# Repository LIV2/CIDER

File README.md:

# CDTV IDE + RAM
IDE + 11.37 Megabyte Fast RAM + Dual Kickstart flash for the CDTV

## Features

- Plugs in to the Diagnostic port
- Autoboot IDE, Kick 1.3 compatible Open Source driver [lide.device](https://github.com/LIV2/lide.device)
- 11.37MB Fast RAM - 1.5MB $C0/Ranger + 8MB Fast + 1.87 Bonus ($A00000)
- Dual Kickstart Flash ROM with Extended ROM, programmable in-system

## Table of contents
1. [Compatibility](#compatibility)
2. [Quick start](#quick-start)
3. [Switch settings](#switch-settings)
    * [DIP Switches](#dip-switches)
    * [JP15](#jp15)
4. [Programming](#programming)
5. [Software](#software)
6. [Common issues](#common-issues)
7. [Ordering pcbs](#ordering-pcbs)
    * [PCB Order details](#pcb-order-details)
    * [PCB Assembly](#pcb-assembly)
    * [Bill of materials](#bill-of-materials)
8. [Pictures](#pictures)
9. [Acknowledgements](#acknowledgements)
10. [License](#license)

## Compatibility

Compatible with kickstart 1.3 and up.

## Quick start
* Remove the power cord from your CDTV
* Ensure the kick flash switch is turned off before using for the first time, all other dip-switches may be enabled if you wish
* Plug into the diag port in your CDTV
* Connect jumper-wire from CDTV JP15 and "To JP15" header, or remove the jumper from the CDTV's JP15 header
* Boot from the CIDER-IDE-Update.adf [here](https://github.com/LIV2/CIDER-Software/releases) to install the IDE ROM
* Download the software tools from the [CIDER-Software](https://github.com/LIV2/cider-software/releases) release page
* Consult the software [documentation](https://github.com/LIV2/CIDER-Software/blob/main/README.md)

## Switch settings
* A500 Mode: Disables the CDTV extended rom
* ROM Select: Selects the second bank of the Kickstart Flash when closed

### DIP Switches
1. Fast RAM enable
2. Ranger / $C0 RAM enable
3. IDE enable
4. Kick flash enable

### JP15
CIDER needs to disable the CDTV's own extended roms when in A500 mode, or when CIDER's Kick flash is enabled so that it can take over this function  
If you don't have a cable to connect this, you can simply remove the JP15 jumper (but the ext rom will then be disabled even if kick flash is switched off)

## Programming

Program the CPLD using this [jed file](https://github.com/LIV2/CIDER/raw/main/Binary/CIDER.jed) - You can find instructions on how to do that [here](https://linuxjedi.co.uk/2020/12/01/programming-xilinx-jtag-from-a-raspberry-pi/)

IDE ROM can be programmed by booting from the latest CIDER-IDE-Update.adf [here](https://github.com/LIV2/CIDER-Software/releases).

## Software

Various software tools for CIDER are available in the [CIDER-Software](https://github.com/LIV2/CIDER-Software) repository, you can find disk images and .lha files under the Releases section.

## Common issues

* **CDTV doesn't boot from IDE:** The original CDTV bootstrap does not boot from hard disks by default, only the builtin scsi.device, floppy or cdrom.  
To boot from the HDD I recommend making use of the 2.35 Extended rom from [CDTV Land](https://cdtvland.com/os235/)

## Ordering PCBs

Download the latest Gerbers.zip from the latest release listed on the right-hand side of this page.

Also included in the release are the placement and bom files needed for JLCPCB's assembly service

### PCB Order details
This PCB has been designed to JLCPCB's 4-layer capabilities so I recommend ordering from them

* Layers: 4
* Surface finish: ENIG
* Remove Order Number: Specify a location

### PCB Assembly
The release files include the relevant BOM and CPL files for JLCPCB's Assembly service  
You can use the following options:  
* PCBA Type: Economic
* Assembly side: Top side
* Tooling Holes: Added by Customer
* Confirm Parts Placement: Yes (I recommend checking that all ICs have pin 1 in the correct location etc)

### Bill of materials
|References|Qty|Value|Footprint|Link|Notes|
|----------|---|-----|---------|----|-----|
|CN1|1|CDTV Connector|KEL 8801-080-170S-F| |Contact KEL to order|
|C1,C3,C4,C6,C7,C8,C10,C11-14,C16-26,C28|23|0.1uF Ceramic|0603|[Mouser](https://www.mouser.com/ProductDetail/80-C603C104K5RAC3121)| |
|C2,C5,C27|3|47uF Tantalum|EIA-3216 KEMET A|[Mouser](https://www.mouser.com/ProductDetail/80-T490A476M10ATE1K)| |
|C9,C15|3|10uF Tantalum|EIA-3216 KEMET A|[Mouser](https://www.mouser.com/ProductDetail/581-TAJA106K016R)| |
|R2,R3,R5-12|10|10K|0603|[Mouser](https://www.mouser.com/ProductDetail/279-CRGH0603J10K)| |
|R13,R14|2|1K|0603|[Mouser](https://www.mouser.com/ProductDetail/791-WR06X102JTL)| |
|R1|1|33|0603|[Mouser](https://www.mouser.com/ProductDetail/279-CRG0603F33R)| |
|R4|1|220|0603|[Mouser](https://www.mouser.com/ProductDetail/71-CRCW0603-220-E3)| |
|D1|1|SMD LED|0603|[Mouser](https://www.mouser.com/ProductDetail/710-150060VS75003)| |
|U3-5|3|74HCT245|TSSOP-20|[Mouser](https://www.mouser.com/ProductDetail/595-SN74HCT245PWR)| |
|U6-7|3|74LVC245|TSSOP-20|[Mouser](https://www.mouser.com/ProductDetail/595-SN74LVC245APWR)| |
|U1|1|AZ1117CR-3.3|SOT-89-3|[Mouser](https://www.mouser.com/ProductDetail/621-AZ1117CR-3.3TRG1)| |
|U2|1|XC95144XL-10TQ100|TQFP-100|[Mouser](https://www.mouser.com/ProductDetail/217-5144XL-10TQG100C)|
|U8|1|8Mx16 SDRAM A3V28S40JTP-60|TSOP-II-54|[Mouser](https://www.mouser.com/ProductDetail/155-A3V28S40JTP-60)|Also suitable:</br> MT48LC8M16</br>W9812G6KH|
|U9|1|29F160|TSOP-I-48|[Mouser](https://www.mouser.com/ProductDetail/913-M29F160FB5AN6F2)| |
|U10|1|39SF010|TSOP-I-32|[Mouser](https://www.mouser.com/ProductDetail/804-39SF010A7CWHE)| |
|U11|1|74LVC1G32|SOT-23-5|[Mouser](https://www.mouser.com/ProductDetail/595-SN74LVC1G32DBVR)| |
|X1|1|50MHz Oscillator|3.2x2.5mm|[Mouser](https://www.mouser.com/ProductDetail/520-ECS-2333-500-BNT)| |
|F1|1|Polyfuse 1A trip, 500mA hold|1206|[Mouser](https://www.mouser.com/ProductDetail/576-1206L075/13.2WR)| |
|SW1|1|Omron A6H-4101|A6H-4101|[Mouser](https://www.mouser.com/ProductDetail/653-A6H-4101)| |
|RN1|1|10K|R Array Convex 4x0603|[Mouser](https://www.mouser.com/ProductDetail/667-EXB-V8V103GV)| |
|RN2-5|4|22 Ohm|R Array Convex 4x0603|[Mouser](https://www.mouser.com/ProductDetail/667-EXB-V8N220JV)| |
|J2-J3|2|Header|2.0mm 1x02 Right-angle| | |
|J5|1|Header|2.54mm 1x03 Right-angle| | |

## Pictures

## Acknowledgements

Thanks to [Stefan Reinauer](https://github.com/reinauer) for the idea to make a CDTV expansion, helping me to develop & test this and for sourcing some Connectors!  
The addition of the Kickstart Flash was inspired by [jbilander](https://github.com/jbilander)'s awesome [Spitfire 2000](https://github.com/jbilander/SF2000)  
Thank you to [Eriond](https://github.com/eriond) for providing the 3D Model of the KEL connector! 

## License

CIDER is licensed under the GPL-2.0 only license

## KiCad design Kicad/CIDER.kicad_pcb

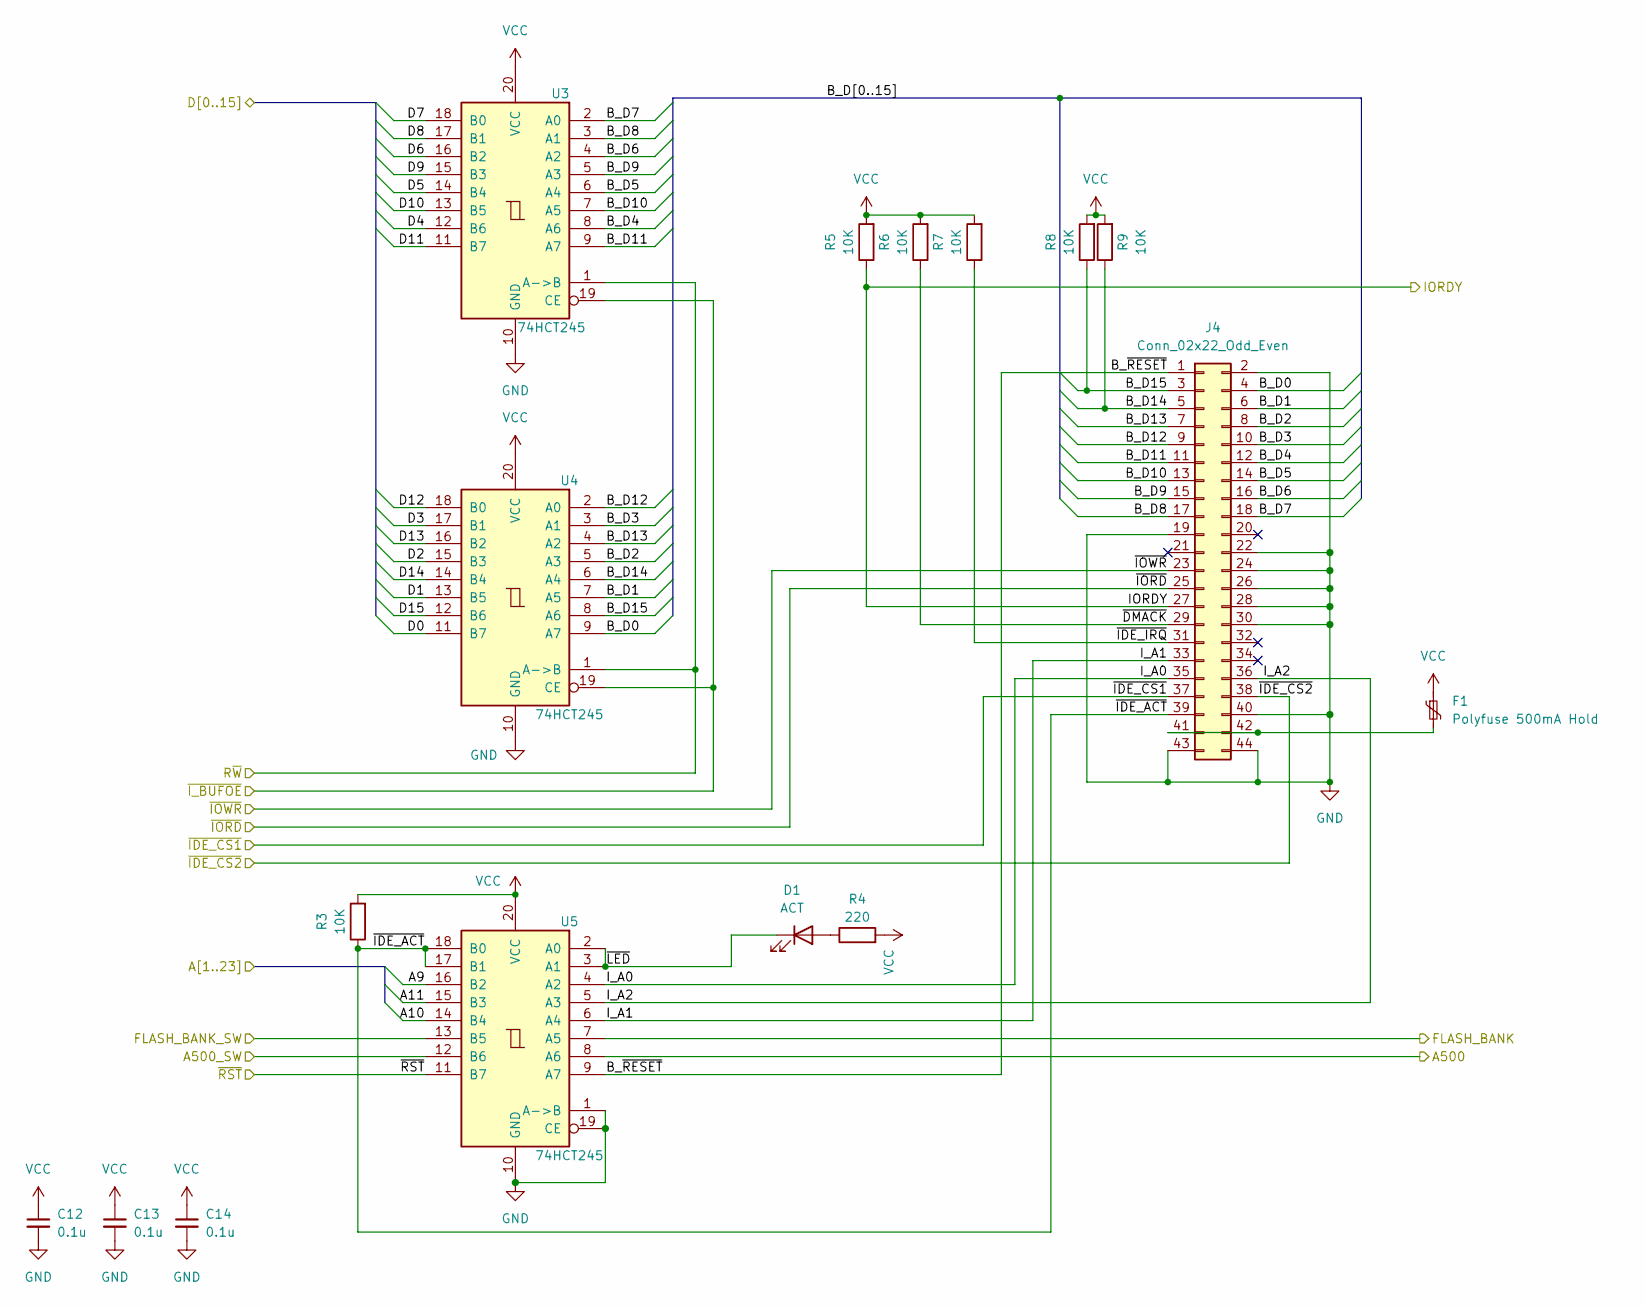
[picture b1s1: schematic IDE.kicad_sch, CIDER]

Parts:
C12, C13, C14: 0.1u; C_0603_1608Metric; LCSC # C14663
D1: ACT; LED_0603_1608Metric; LCSC # C264450
F1: Polyfuse 500mA Hold; Fuse_1206_3216Metric; LCSC # C151162
J4: Conn_02x22_Odd_Even; PinHeader_2x22_P2.00mm_Vertical
R3, R5, R6, R7, R8, R9: 10K; R_0603_1608Metric; LCSC # C25804
R4: 220; R_0603_1608Metric; LCSC # C22962
U3, U4, U5: 74HCT245; TSSOP-20_4.4x6.5mm_P0.65mm; LCSC # C6779

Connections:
/Amiga+CPLD/A9: U5.16 (B2); also elsewhere on the board
/Amiga+CPLD/A10: U5.14 (B4); also elsewhere on the board
/Amiga+CPLD/A11: U5.15 (B3); also elsewhere on the board
/Amiga+CPLD/A500: U5.8 (A6); also elsewhere on the board
/Amiga+CPLD/A500_SW: U5.12 (B6); also elsewhere on the board
/Amiga+CPLD/D0: U4.11 (B7); also elsewhere on the board
/Amiga+CPLD/D1: U4.13 (B5); also elsewhere on the board
/Amiga+CPLD/D2: U4.15 (B3); also elsewhere on the board
/Amiga+CPLD/D3: U4.17 (B1); also elsewhere on the board
/Amiga+CPLD/D4: U3.12 (B6); also elsewhere on the board
/Amiga+CPLD/D5: U3.14 (B4); also elsewhere on the board
/Amiga+CPLD/D6: U3.16 (B2); also elsewhere on the board
/Amiga+CPLD/D7: U3.18 (B0); also elsewhere on the board
/Amiga+CPLD/D8: U3.17 (B1); also elsewhere on the board
/Amiga+CPLD/D9: U3.15 (B3); also elsewhere on the board
/Amiga+CPLD/D10: U3.13 (B5); also elsewhere on the board
/Amiga+CPLD/D11: U3.11 (B7); also elsewhere on the board
/Amiga+CPLD/D12: U4.18 (B0); also elsewhere on the board
/Amiga+CPLD/D13: U4.16 (B2); also elsewhere on the board
/Amiga+CPLD/D14: U4.14 (B4); also elsewhere on the board
/Amiga+CPLD/D15: U4.12 (B6); also elsewhere on the board
/Amiga+CPLD/FLASH_BANK: U5.7 (A5); also elsewhere on the board
/Amiga+CPLD/FLASH_BANK_SW: U5.13 (B5); also elsewhere on the board
/Amiga+CPLD/IORDY: J4.27, R5.1; also elsewhere on the board
/Amiga+CPLD/R~W: U3.1 (A->B), U4.1 (A->B); also elsewhere on the board
/Amiga+CPLD/~IDE_CS1: J4.37; also elsewhere on the board
/Amiga+CPLD/~IDE_CS2: J4.38; also elsewhere on the board
/Amiga+CPLD/~IORD: J4.25; also elsewhere on the board
/Amiga+CPLD/~IOWR: J4.23; also elsewhere on the board
/Amiga+CPLD/~I_BUFOE: U3.19 (CE), U4.19 (CE); also elsewhere on the board
/Amiga+CPLD/~RST: U5.11 (B7); also elsewhere on the board
/IDE/B_D0: J4.4, U4.9 (A7)
/IDE/B_D1: J4.6, U4.7 (A5)
/IDE/B_D2: J4.8, U4.5 (A3)
/IDE/B_D3: J4.10, U4.3 (A1)
/IDE/B_D4: J4.12, U3.8 (A6)
/IDE/B_D5: J4.14, U3.6 (A4)
/IDE/B_D6: J4.16, U3.4 (A2)
/IDE/B_D7: J4.18, U3.2 (A0)
/IDE/B_D8: J4.17, U3.3 (A1)
/IDE/B_D9: J4.15, U3.5 (A3)
/IDE/B_D10: J4.13, U3.7 (A5)
/IDE/B_D11: J4.11, U3.9 (A7)
/IDE/B_D12: J4.9, U4.2 (A0)
/IDE/B_D13: J4.7, U4.4 (A2)
/IDE/B_D14: J4.5, R9.1, U4.6 (A4)
/IDE/B_D15: J4.3, R8.1, U4.8 (A6)
/IDE/B_~RESET: J4.1, U5.9 (A7)
/IDE/I_A0: J4.35, U5.4 (A2)
/IDE/I_A1: J4.33, U5.6 (A4)
/IDE/I_A2: J4.36, U5.5 (A3)
/IDE/~DMACK: J4.29, R6.1
/IDE/~IDE_ACT: J4.39, R3.1, U5.17 (B1), U5.18 (B0)
/IDE/~IDE_IRQ: J4.31, R7.1
/IDE/~LED: D1.1 (K), U5.2 (A0), U5.3 (A1)
GND: C12.2, C13.2, C14.2, J4.2, J4.19, J4.22, J4.24, J4.26, J4.28, J4.30, J4.40, J4.43, J4.44, U3.10 (GND), U4.10 (GND), U5.1 (A->B), U5.10 (GND), U5.19 (CE); also elsewhere on the board
unnamed: D1.2 (A), R4.1
unnamed: F1.2, J4.41, J4.42
VCC: C12.1, C13.1, C14.1, F1.1, R3.2, R4.2, R5.2, R6.2, R7.2, R8.2, R9.2, U3.20 (VCC), U4.20 (VCC), U5.20 (VCC); also elsewhere on the board

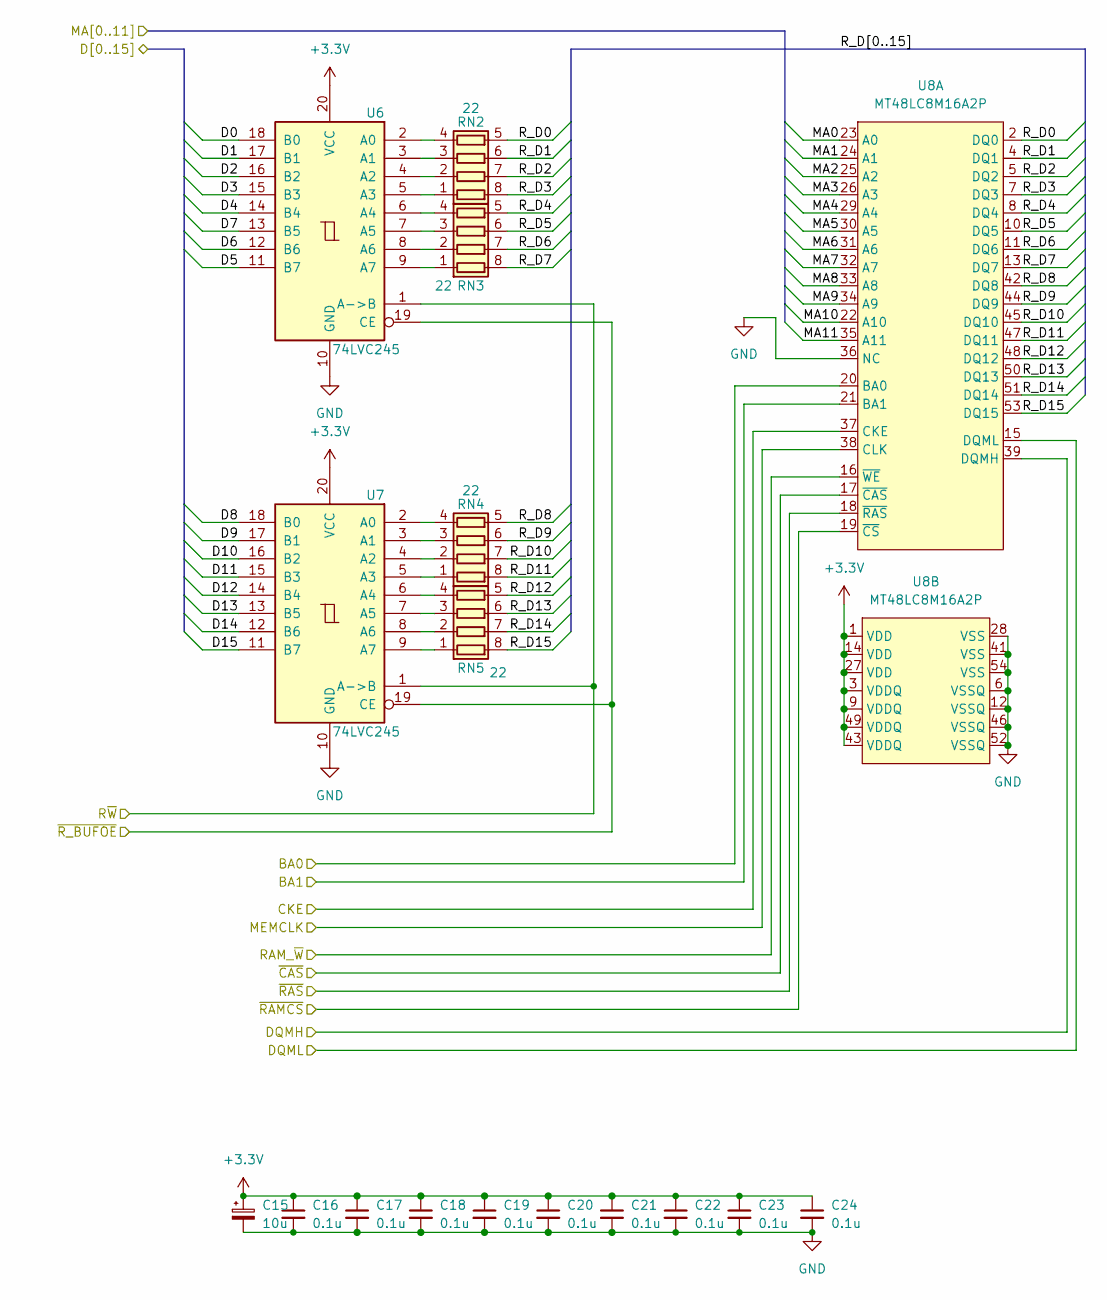
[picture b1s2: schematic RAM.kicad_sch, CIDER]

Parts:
C15: 10u; CP_EIA-3216-18_Kemet-A; LCSC # C7171
C16, C17, C18, C19, C20, C21, C22, C23, C24: 0.1u; C_0603_1608Metric; LCSC # C14663
RN2, RN3, RN4, RN5: 22; R_Array_Convex_4x0603; LCSC # C107373
U6, U7: 74LVC245; TSSOP-20_4.4x6.5mm_P0.65mm; LCSC # C7848
U8: MT48LC8M16A2P; TSOP-II-54_22.2x10.16mm_P0.8mm; LCSC # C62379

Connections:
/Amiga+CPLD/BA0: U8.20 (BA0); also elsewhere on the board
/Amiga+CPLD/BA1: U8.21 (BA1); also elsewhere on the board
/Amiga+CPLD/CKE: U8.37 (CKE); also elsewhere on the board
/Amiga+CPLD/D0: U6.18 (B0); also elsewhere on the board
/Amiga+CPLD/D1: U6.17 (B1); also elsewhere on the board
/Amiga+CPLD/D2: U6.16 (B2); also elsewhere on the board
/Amiga+CPLD/D3: U6.15 (B3); also elsewhere on the board
/Amiga+CPLD/D4: U6.14 (B4); also elsewhere on the board
/Amiga+CPLD/D5: U6.11 (B7); also elsewhere on the board
/Amiga+CPLD/D6: U6.12 (B6); also elsewhere on the board
/Amiga+CPLD/D7: U6.13 (B5); also elsewhere on the board
/Amiga+CPLD/D8: U7.18 (B0); also elsewhere on the board
/Amiga+CPLD/D9: U7.17 (B1); also elsewhere on the board
/Amiga+CPLD/D10: U7.16 (B2); also elsewhere on the board
/Amiga+CPLD/D11: U7.15 (B3); also elsewhere on the board
/Amiga+CPLD/D12: U7.14 (B4); also elsewhere on the board
/Amiga+CPLD/D13: U7.13 (B5); also elsewhere on the board
/Amiga+CPLD/D14: U7.12 (B6); also elsewhere on the board
/Amiga+CPLD/D15: U7.11 (B7); also elsewhere on the board
/Amiga+CPLD/DQMH: U8.39 (DQMH); also elsewhere on the board
/Amiga+CPLD/DQML: U8.15 (DQML); also elsewhere on the board
/Amiga+CPLD/MA0: U8.23 (A0); also elsewhere on the board
/Amiga+CPLD/MA1: U8.24 (A1); also elsewhere on the board
/Amiga+CPLD/MA2: U8.25 (A2); also elsewhere on the board
/Amiga+CPLD/MA3: U8.26 (A3); also elsewhere on the board
/Amiga+CPLD/MA4: U8.29 (A4); also elsewhere on the board
/Amiga+CPLD/MA5: U8.30 (A5); also elsewhere on the board
/Amiga+CPLD/MA6: U8.31 (A6); also elsewhere on the board
/Amiga+CPLD/MA7: U8.32 (A7); also elsewhere on the board
/Amiga+CPLD/MA8: U8.33 (A8); also elsewhere on the board
/Amiga+CPLD/MA9: U8.34 (A9); also elsewhere on the board
/Amiga+CPLD/MA10: U8.22 (A10); also elsewhere on the board
/Amiga+CPLD/MA11: U8.35 (A11); also elsewhere on the board
/Amiga+CPLD/MEMCLK: U8.38 (CLK); also elsewhere on the board
/Amiga+CPLD/RAM_~W: U8.16 (~WE); also elsewhere on the board
/Amiga+CPLD/R~W: U6.1 (A->B), U7.1 (A->B); also elsewhere on the board
/Amiga+CPLD/~CAS: U8.17 (~CAS); also elsewhere on the board
/Amiga+CPLD/~RAMCS: U8.19 (~CS); also elsewhere on the board
/Amiga+CPLD/~RAS: U8.18 (~RAS); also elsewhere on the board
/Amiga+CPLD/~R_BUFOE: U6.19 (CE), U7.19 (CE); also elsewhere on the board
/RAM/R_D0: RN2.5 (R4.2), U8.2 (DQ0)
/RAM/R_D1: RN2.6 (R3.2), U8.4 (DQ1)
/RAM/R_D2: RN2.7 (R2.2), U8.5 (DQ2)
/RAM/R_D3: RN2.8 (R1.2), U8.7 (DQ3)
/RAM/R_D4: RN3.5 (R4.2), U8.8 (DQ4)
/RAM/R_D5: RN3.6 (R3.2), U8.10 (DQ5)
/RAM/R_D6: RN3.7 (R2.2), U8.11 (DQ6)
/RAM/R_D7: RN3.8 (R1.2), U8.13 (DQ7)
/RAM/R_D8: RN4.5 (R4.2), U8.42 (DQ8)
/RAM/R_D9: RN4.6 (R3.2), U8.44 (DQ9)
/RAM/R_D10: RN4.7 (R2.2), U8.45 (DQ10)
/RAM/R_D11: RN4.8 (R1.2), U8.47 (DQ11)
/RAM/R_D12: RN5.5 (R4.2), U8.48 (DQ12)
/RAM/R_D13: RN5.6 (R3.2), U8.50 (DQ13)
/RAM/R_D14: RN5.7 (R2.2), U8.51 (DQ14)
/RAM/R_D15: RN5.8 (R1.2), U8.53 (DQ15)
GND: C15.2, C16.2, C17.2, C18.2, C19.2, C20.2, C21.2, C22.2, C23.2, C24.2, U6.10 (GND), U7.10 (GND), U8.6 (VSSQ), U8.12 (VSSQ), U8.28 (VSS), U8.36 (NC), U8.41 (VSS), U8.46 (VSSQ), U8.52 (VSSQ), U8.54 (VSS); also elsewhere on the board
unnamed: RN2.1 (R1.1), U6.5 (A3)
unnamed: RN2.2 (R2.1), U6.4 (A2)
unnamed: RN2.3 (R3.1), U6.3 (A1)
unnamed: RN2.4 (R4.1), U6.2 (A0)
unnamed: RN3.1 (R1.1), U6.9 (A7)
unnamed: RN3.2 (R2.1), U6.8 (A6)
unnamed: RN3.3 (R3.1), U6.7 (A5)
unnamed: RN3.4 (R4.1), U6.6 (A4)
unnamed: RN4.1 (R1.1), U7.5 (A3)
unnamed: RN4.2 (R2.1), U7.4 (A2)
unnamed: RN4.3 (R3.1), U7.3 (A1)
unnamed: RN4.4 (R4.1), U7.2 (A0)
unnamed: RN5.1 (R1.1), U7.9 (A7)
unnamed: RN5.2 (R2.1), U7.8 (A6)
unnamed: RN5.3 (R3.1), U7.7 (A5)
unnamed: RN5.4 (R4.1), U7.6 (A4)

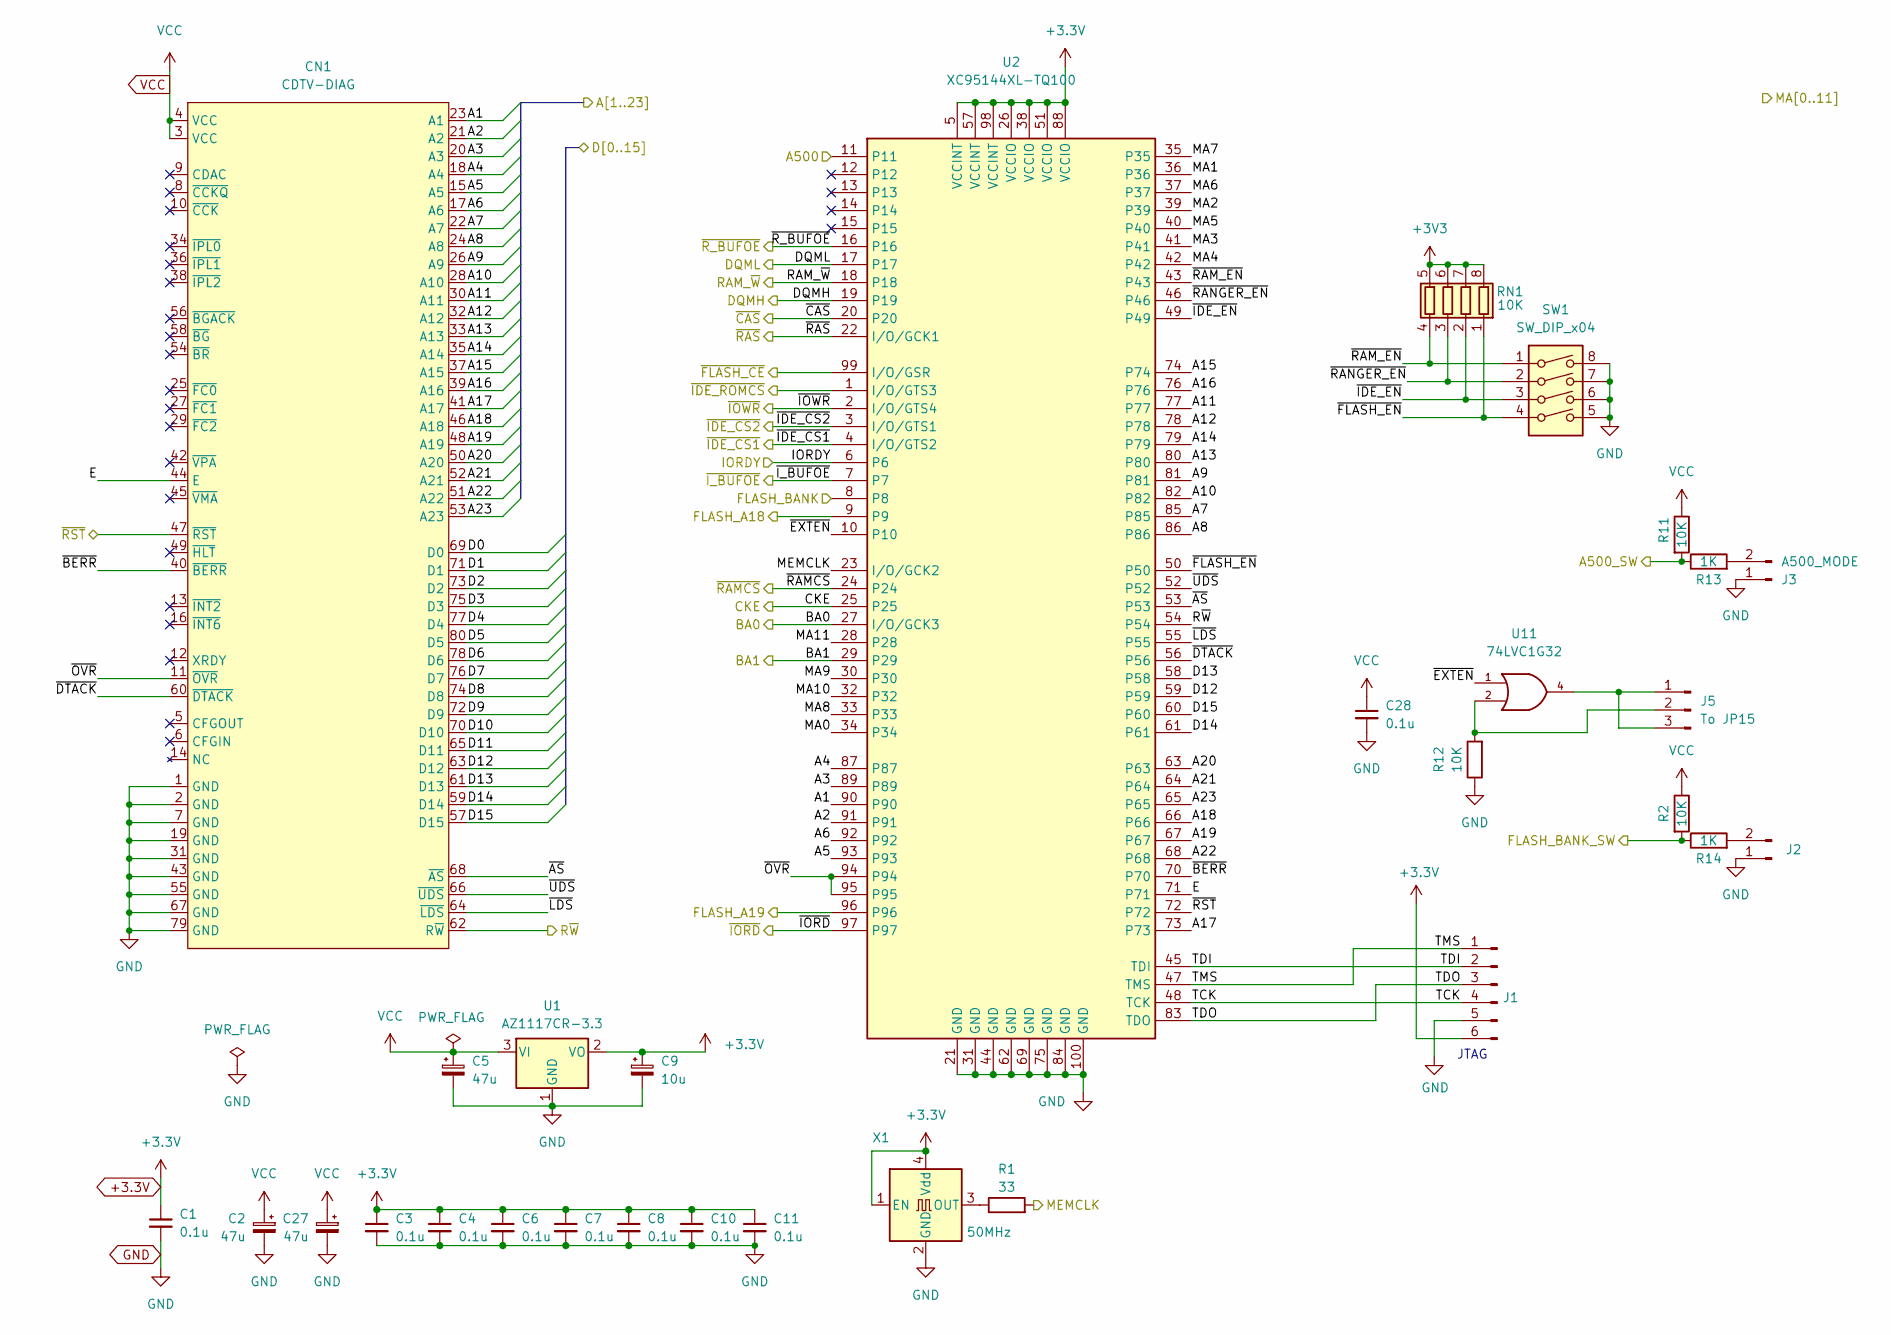
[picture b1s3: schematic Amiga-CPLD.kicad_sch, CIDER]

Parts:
C1, C3, C4, C6, C7, C8, C10, C11, C28: 0.1u; C_0603_1608Metric; LCSC # C14663
C2, C5, C27: 47u; CP_EIA-3216-18_Kemet-A; LCSC # C193224
C9: 10u; CP_EIA-3216-18_Kemet-A; LCSC # C7171
CN1: CDTV-DIAG; KEL-8800-080-170S
J1: JTAG; PinHeader_1x06_P2.54mm_Vertical
J2: LED; PinHeader_1x02_P2.00mm_Vertical
J3: A500_MODE; PinHeader_1x02_P2.00mm_Vertical
J5: To JP15; PinHeader_1x03_P2.54mm_Horizontal
R1: 33; R_0603_1608Metric; LCSC # C23140
R2, R11, R12: 10K; R_0603_1608Metric; LCSC # C25804
R13, R14: 1K; R_0603_1608Metric; LCSC # C21190
RN1: 10K; R_Array_Convex_4x0603; LCSC # C110924
SW1: SW_DIP_x04; SW_DIP_SPSTx04_Slide_Omron_A6H-4101_W6.15mm_P1.27mm; LCSC # C397291
U1: AZ1117CR-3.3; SOT-89-3; LCSC # C460428
U2: XC95144XL-TQ100; TQFP-100_14x14mm_P0.5mm; LCSC # C45126
U11: 74LVC1G32; SOT-23-5; LCSC # C10096
X1: 50MHz; Oscillator_SMD_Abracon_ASE-4Pin_3.2x2.5mm_HandSoldering; LCSC # C46327

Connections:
/Amiga+CPLD/A1: CN1.23 (A1), U2.90; also elsewhere on the board
/Amiga+CPLD/A2: CN1.21 (A2), U2.91; also elsewhere on the board
/Amiga+CPLD/A3: CN1.20 (A3), U2.89; also elsewhere on the board
/Amiga+CPLD/A4: CN1.18 (A4), U2.87; also elsewhere on the board
/Amiga+CPLD/A5: CN1.15 (A5), U2.93; also elsewhere on the board
/Amiga+CPLD/A6: CN1.17 (A6), U2.92; also elsewhere on the board
/Amiga+CPLD/A7: CN1.22 (A7), U2.85; also elsewhere on the board
/Amiga+CPLD/A8: CN1.24 (A8), U2.86; also elsewhere on the board
/Amiga+CPLD/A9: CN1.26 (A9), U2.81; also elsewhere on the board
/Amiga+CPLD/A10: CN1.28 (A10), U2.82; also elsewhere on the board
/Amiga+CPLD/A11: CN1.30 (A11), U2.77; also elsewhere on the board
/Amiga+CPLD/A12: CN1.32 (A12), U2.78; also elsewhere on the board
/Amiga+CPLD/A13: CN1.33 (A13), U2.80; also elsewhere on the board
/Amiga+CPLD/A14: CN1.35 (A14), U2.79; also elsewhere on the board
/Amiga+CPLD/A15: CN1.37 (A15), U2.74; also elsewhere on the board
/Amiga+CPLD/A16: CN1.39 (A16), U2.76; also elsewhere on the board
/Amiga+CPLD/A17: CN1.41 (A17), U2.73; also elsewhere on the board
/Amiga+CPLD/A18: CN1.46 (A18), U2.66; also elsewhere on the board
/Amiga+CPLD/A19: CN1.48 (A19), U2.67
/Amiga+CPLD/A20: CN1.50 (A20), U2.63
/Amiga+CPLD/A21: CN1.52 (A21), U2.64
/Amiga+CPLD/A22: CN1.51 (A22), U2.68
/Amiga+CPLD/A23: CN1.53 (A23), U2.65
/Amiga+CPLD/A500: U2.11; also elsewhere on the board
/Amiga+CPLD/A500_SW: R11.2, R13.1; also elsewhere on the board
/Amiga+CPLD/BA0: U2.27 (I/O/GCK3); also elsewhere on the board
/Amiga+CPLD/BA1: U2.29; also elsewhere on the board
/Amiga+CPLD/CKE: U2.25; also elsewhere on the board
/Amiga+CPLD/D0: CN1.69 (D0); also elsewhere on the board
/Amiga+CPLD/D1: CN1.71 (D1); also elsewhere on the board
/Amiga+CPLD/D2: CN1.73 (D2); also elsewhere on the board
/Amiga+CPLD/D3: CN1.75 (D3); also elsewhere on the board
/Amiga+CPLD/D4: CN1.77 (D4); also elsewhere on the board
/Amiga+CPLD/D5: CN1.80 (D5); also elsewhere on the board
/Amiga+CPLD/D6: CN1.78 (D6); also elsewhere on the board
/Amiga+CPLD/D7: CN1.76 (D7); also elsewhere on the board
/Amiga+CPLD/D8: CN1.74 (D8); also elsewhere on the board
/Amiga+CPLD/D9: CN1.72 (D9); also elsewhere on the board
/Amiga+CPLD/D10: CN1.70 (D10); also elsewhere on the board
/Amiga+CPLD/D11: CN1.65 (D11); also elsewhere on the board
/Amiga+CPLD/D12: CN1.63 (D12), U2.59; also elsewhere on the board
/Amiga+CPLD/D13: CN1.61 (D13), U2.58; also elsewhere on the board
/Amiga+CPLD/D14: CN1.59 (D14), U2.61; also elsewhere on the board
/Amiga+CPLD/D15: CN1.57 (D15), U2.60; also elsewhere on the board
/Amiga+CPLD/DQMH: U2.19; also elsewhere on the board
/Amiga+CPLD/DQML: U2.17; also elsewhere on the board
/Amiga+CPLD/E: CN1.44 (E), U2.71
/Amiga+CPLD/FLASH_A18: U2.9; also elsewhere on the board
/Amiga+CPLD/FLASH_A19: U2.96; also elsewhere on the board
/Amiga+CPLD/FLASH_BANK: U2.8; also elsewhere on the board
/Amiga+CPLD/FLASH_BANK_SW: R2.2, R14.1; also elsewhere on the board
/Amiga+CPLD/IORDY: U2.6; also elsewhere on the board
/Amiga+CPLD/MA0: U2.34; also elsewhere on the board
/Amiga+CPLD/MA1: U2.36; also elsewhere on the board
/Amiga+CPLD/MA2: U2.39; also elsewhere on the board
/Amiga+CPLD/MA3: U2.41; also elsewhere on the board
/Amiga+CPLD/MA4: U2.42; also elsewhere on the board
/Amiga+CPLD/MA5: U2.40; also elsewhere on the board
/Amiga+CPLD/MA6: U2.37; also elsewhere on the board
/Amiga+CPLD/MA7: U2.35; also elsewhere on the board
/Amiga+CPLD/MA8: U2.33; also elsewhere on the board
/Amiga+CPLD/MA9: U2.30; also elsewhere on the board
/Amiga+CPLD/MA10: U2.32; also elsewhere on the board
/Amiga+CPLD/MA11: U2.28; also elsewhere on the board
/Amiga+CPLD/MEMCLK: R1.2, U2.23 (I/O/GCK2); also elsewhere on the board
/Amiga+CPLD/RAM_~W: U2.18; also elsewhere on the board
/Amiga+CPLD/R~W: CN1.62 (R~W), U2.54; also elsewhere on the board
/Amiga+CPLD/TCK: J1.4, U2.48 (TCK)
/Amiga+CPLD/TDI: J1.2, U2.45 (TDI)
/Amiga+CPLD/TDO: J1.3, U2.83 (TDO)
/Amiga+CPLD/TMS: J1.1, U2.47 (TMS)
/Amiga+CPLD/~AS: CN1.68 (~AS), U2.53
/Amiga+CPLD/~BERR: CN1.40 (~BERR), U2.70
/Amiga+CPLD/~CAS: U2.20; also elsewhere on the board
/Amiga+CPLD/~DTACK: CN1.60 (~DTACK), U2.56
/Amiga+CPLD/~EXTEN: U2.10, U11.1
/Amiga+CPLD/~FLASH_CE: U2.99 (I/O/GSR); also elsewhere on the board
/Amiga+CPLD/~FLASH_EN: RN1.1 (R1.1), SW1.4, U2.50
/Amiga+CPLD/~IDE_CS1: U2.4 (I/O/GTS2); also elsewhere on the board
/Amiga+CPLD/~IDE_CS2: U2.3 (I/O/GTS1); also elsewhere on the board
/Amiga+CPLD/~IDE_EN: RN1.2 (R2.1), SW1.3, U2.49
/Amiga+CPLD/~IDE_ROMCS: U2.1 (I/O/GTS3); also elsewhere on the board
/Amiga+CPLD/~IORD: U2.97; also elsewhere on the board
/Amiga+CPLD/~IOWR: U2.2 (I/O/GTS4); also elsewhere on the board
/Amiga+CPLD/~I_BUFOE: U2.7; also elsewhere on the board
/Amiga+CPLD/~LDS: CN1.64 (~LDS), U2.55
/Amiga+CPLD/~OVR: CN1.11 (~OVR), U2.94, U2.95
/Amiga+CPLD/~RAMCS: U2.24; also elsewhere on the board
/Amiga+CPLD/~RAM_EN: RN1.4 (R4.1), SW1.1, U2.43
/Amiga+CPLD/~RANGER_EN: RN1.3 (R3.1), SW1.2, U2.46
/Amiga+CPLD/~RAS: U2.22 (I/O/GCK1); also elsewhere on the board
/Amiga+CPLD/~RST: CN1.47 (~RST), U2.72; also elsewhere on the board
/Amiga+CPLD/~R_BUFOE: U2.16; also elsewhere on the board
/Amiga+CPLD/~UDS: CN1.66 (~UDS), U2.52
GND: C1.2, C2.2, C3.2, C4.2, C5.2, C6.2, C7.2, C8.2, C9.2, C10.2, C11.2, C27.2, C28.2, CN1.1 (GND), CN1.2 (GND), CN1.7 (GND), CN1.19 (GND), CN1.31 (GND), CN1.43 (GND), CN1.55 (GND), CN1.67 (GND), CN1.79 (GND), J1.5, J2.1, J3.1, R12.1, SW1.5, SW1.6, SW1.7, SW1.8, U1.1 (GND), U2.21 (GND), U2.31 (GND), U2.44 (GND), U2.62 (GND), U2.69 (GND), U2.75 (GND), U2.84 (GND), U2.100 (GND), U11.3 (GND), X1.2 (GND); also elsewhere on the board
unnamed: J2.2, R14.2
unnamed: J3.2, R13.2
unnamed: J5.1, J5.3, U11.4
unnamed: J5.2, R12.2, U11.2
unnamed: R1.1, X1.3 (OUT)
VCC: C2.1, C5.1, C27.1, C28.1, CN1.3 (VCC), CN1.4 (VCC), R2.1, R11.1, U1.3 (VI), U11.5 (VCC); also elsewhere on the board

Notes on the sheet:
JTAG

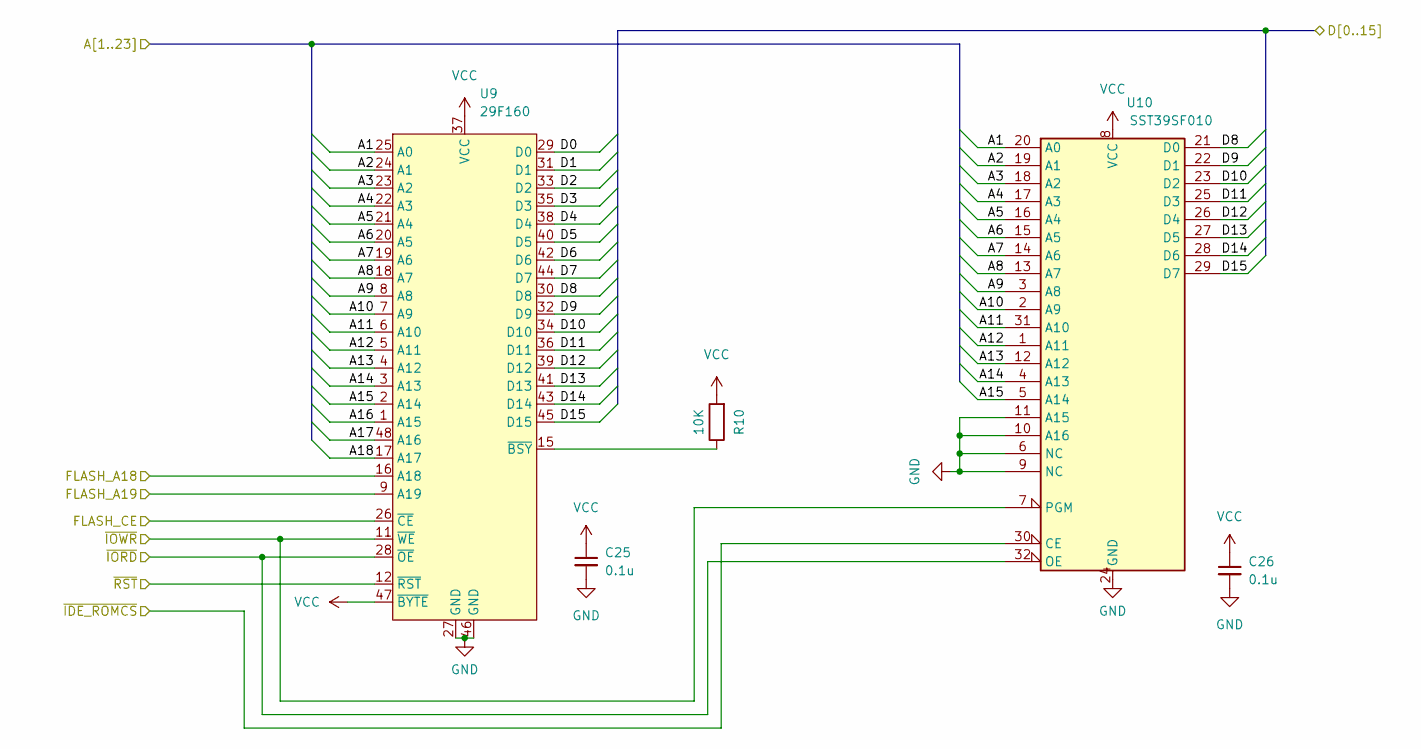
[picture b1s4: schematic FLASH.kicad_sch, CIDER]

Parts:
C25, C26: 0.1u; C_0603_1608Metric; LCSC # C14663
R10: 10K; R_0603_1608Metric; LCSC # C25804
U9: 29F160; TSOP-I-48_18.4x12mm_P0.5mm
U10: SST39SF010; TSOP-I-32_11.8x8mm_P0.5mm

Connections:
/Amiga+CPLD/A1: U9.25 (A0), U10.20 (A0); also elsewhere on the board
/Amiga+CPLD/A2: U9.24 (A1), U10.19 (A1); also elsewhere on the board
/Amiga+CPLD/A3: U9.23 (A2), U10.18 (A2); also elsewhere on the board
/Amiga+CPLD/A4: U9.22 (A3), U10.17 (A3); also elsewhere on the board
/Amiga+CPLD/A5: U9.21 (A4), U10.16 (A4); also elsewhere on the board
/Amiga+CPLD/A6: U9.20 (A5), U10.15 (A5); also elsewhere on the board
/Amiga+CPLD/A7: U9.19 (A6), U10.14 (A6); also elsewhere on the board
/Amiga+CPLD/A8: U9.18 (A7), U10.13 (A7); also elsewhere on the board
/Amiga+CPLD/A9: U9.8 (A8), U10.3 (A8); also elsewhere on the board
/Amiga+CPLD/A10: U9.7 (A9), U10.2 (A9); also elsewhere on the board
/Amiga+CPLD/A11: U9.6 (A10), U10.31 (A10); also elsewhere on the board
/Amiga+CPLD/A12: U9.5 (A11), U10.1 (A11); also elsewhere on the board
/Amiga+CPLD/A13: U9.4 (A12), U10.12 (A12); also elsewhere on the board
/Amiga+CPLD/A14: U9.3 (A13), U10.4 (A13); also elsewhere on the board
/Amiga+CPLD/A15: U9.2 (A14), U10.5 (A14); also elsewhere on the board
/Amiga+CPLD/A16: U9.1 (A15); also elsewhere on the board
/Amiga+CPLD/A17: U9.48 (A16); also elsewhere on the board
/Amiga+CPLD/A18: U9.17 (A17); also elsewhere on the board
/Amiga+CPLD/D0: U9.29 (D0); also elsewhere on the board
/Amiga+CPLD/D1: U9.31 (D1); also elsewhere on the board
/Amiga+CPLD/D2: U9.33 (D2); also elsewhere on the board
/Amiga+CPLD/D3: U9.35 (D3); also elsewhere on the board
/Amiga+CPLD/D4: U9.38 (D4); also elsewhere on the board
/Amiga+CPLD/D5: U9.40 (D5); also elsewhere on the board
/Amiga+CPLD/D6: U9.42 (D6); also elsewhere on the board
/Amiga+CPLD/D7: U9.44 (D7); also elsewhere on the board
/Amiga+CPLD/D8: U9.30 (D8), U10.21 (D0); also elsewhere on the board
/Amiga+CPLD/D9: U9.32 (D9), U10.22 (D1); also elsewhere on the board
/Amiga+CPLD/D10: U9.34 (D10), U10.23 (D2); also elsewhere on the board
/Amiga+CPLD/D11: U9.36 (D11), U10.25 (D3); also elsewhere on the board
/Amiga+CPLD/D12: U9.39 (D12), U10.26 (D4); also elsewhere on the board
/Amiga+CPLD/D13: U9.41 (D13), U10.27 (D5); also elsewhere on the board
/Amiga+CPLD/D14: U9.43 (D14), U10.28 (D6); also elsewhere on the board
/Amiga+CPLD/D15: U9.45 (D15), U10.29 (D7); also elsewhere on the board
/Amiga+CPLD/FLASH_A18: U9.16 (A18); also elsewhere on the board
/Amiga+CPLD/FLASH_A19: U9.9 (A19); also elsewhere on the board
/Amiga+CPLD/~FLASH_CE: U9.26 (~CE); also elsewhere on the board
/Amiga+CPLD/~IDE_ROMCS: U10.30 (CE); also elsewhere on the board
/Amiga+CPLD/~IORD: U9.28 (~OE), U10.32 (OE); also elsewhere on the board
/Amiga+CPLD/~IOWR: U9.11 (~WE), U10.7 (PGM); also elsewhere on the board
/Amiga+CPLD/~RST: U9.12 (~RST); also elsewhere on the board
GND: C25.2, C26.2, U9.27 (GND), U9.46 (GND), U10.6 (NC), U10.9 (NC), U10.10 (A16), U10.11 (A15), U10.24 (GND); also elsewhere on the board
unnamed: R10.1, U9.15 (~BSY)
VCC: C25.1, C26.1, R10.2, U9.37 (VCC), U9.47 (~BYTE), U10.8 (VCC); also elsewhere on the board

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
